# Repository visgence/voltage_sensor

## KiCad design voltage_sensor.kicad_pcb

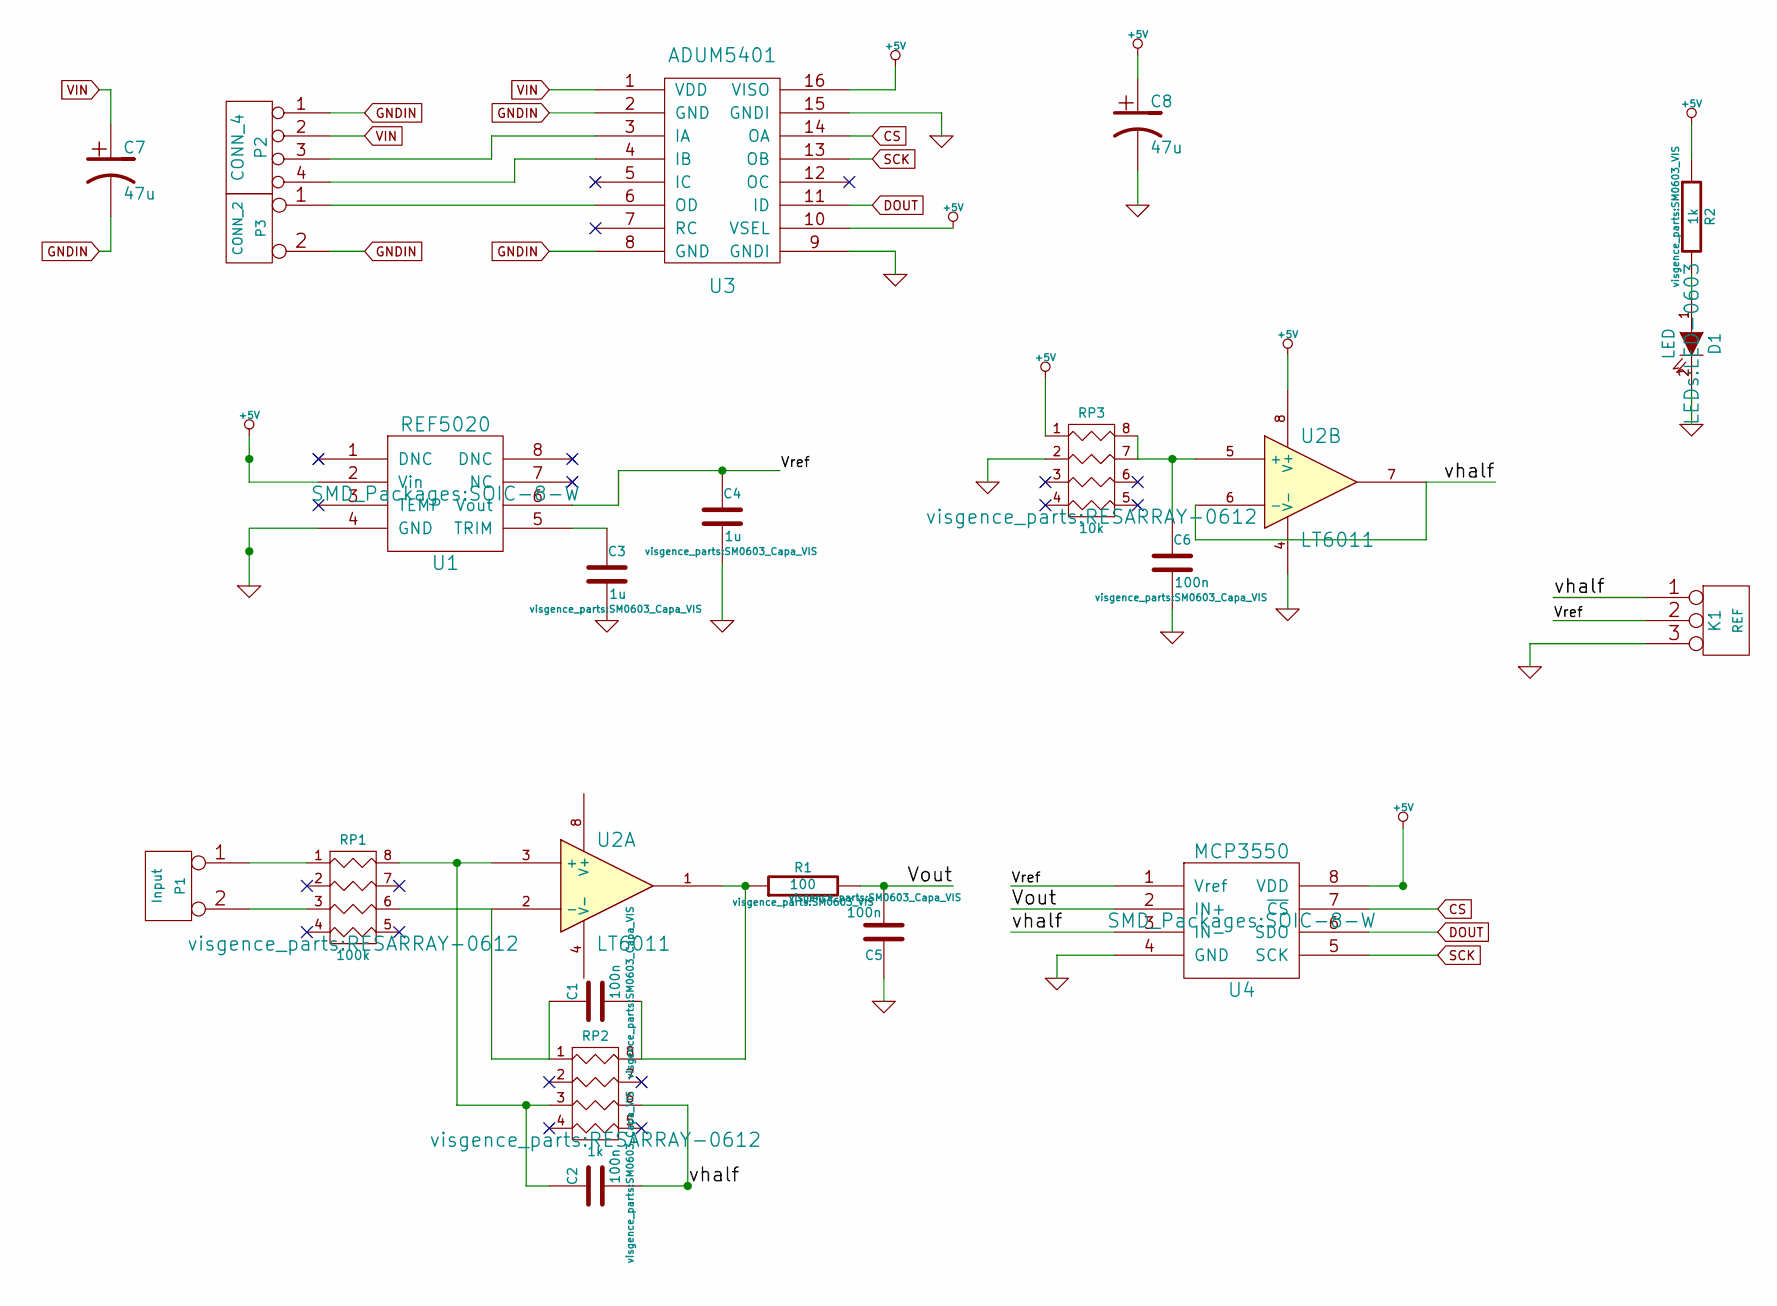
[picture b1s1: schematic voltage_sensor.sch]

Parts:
C1, C2, C5, C6: 100n; SM0603_Capa_VIS
C3, C4: 1u; SM0603_Capa_VIS
C7, C8: 47u; SM1206POL_VIS
D1: LED; LED-0603
K1: REF; Pin_Header_Straight_1x03
P1: Input; bornier2
P2: CONN_4; Term3.5-4
P3: CONN_2; Term3.5-2
R1: 100; SM0603_VIS
R2: 1k; SM0603_VIS
RP1: 100k; RESARRAY-0612
RP2: 1k; RESARRAY-0612
RP3: 10k; RESARRAY-0612
U1: REF5020; SOIC-8-W
U2: LT6011; SOIC-8-W
U3: ADUM5401; SO-16-W
U4: MCP3550; SOIC-8-W

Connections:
+5V: C8.1, R2.1, RP3.1, U1.2 (Vin), U2.8 (V+), U3.10 (VSEL), U3.16 (VISO), U4.8 (VDD)
/Vout: C5.2, R1.2, U4.2 (IN+)
/Vref: C4.1, K1.2 (PM), U1.6 (Vout), U4.1 (Vref)
/vhalf: C2.2, K1.1, RP2.6 (R3), U2.6 (-), U2.7, U4.3 (IN-)
CS: U3.14 (OA), U4.7 (~CS)
DOUT: U3.11 (ID), U4.6 (SDO)
GND: C3.2, C4.2, C5.1, C6.2, C8.2, D1.2 (K), K1.3, RP3.2, U1.4 (GND), U2.4 (V-), U3.9 (GNDI), U3.15 (GNDI), U4.4 (GND)
GNDIN: C7.2, P2.1, P3.2 (PM), U3.2 (GND), U3.8 (GND)
unnamed: C1.1, RP1.6 (R3), RP2.1, U2.2 (-)
unnamed: C1.2, R1.1, RP2.8 (R1), U2.1
unnamed: C2.1, RP1.8 (R1), RP2.3, U2.3 (+)
unnamed: C3.1, U1.5 (TRIM)
unnamed: C6.1, RP3.7 (R2), RP3.8 (R1), U2.5 (+)
unnamed: D1.1 (A), R2.2
unnamed: P1.1, RP1.1
unnamed: P1.2 (PM), RP1.3
unnamed: P2.3, U3.3 (IA)
unnamed: P2.4, U3.4 (IB)
unnamed: P3.1, U3.6 (OD)
SCK: U3.13 (OB), U4.5 (SCK)
VIN: C7.1, P2.2, U3.1 (VDD)

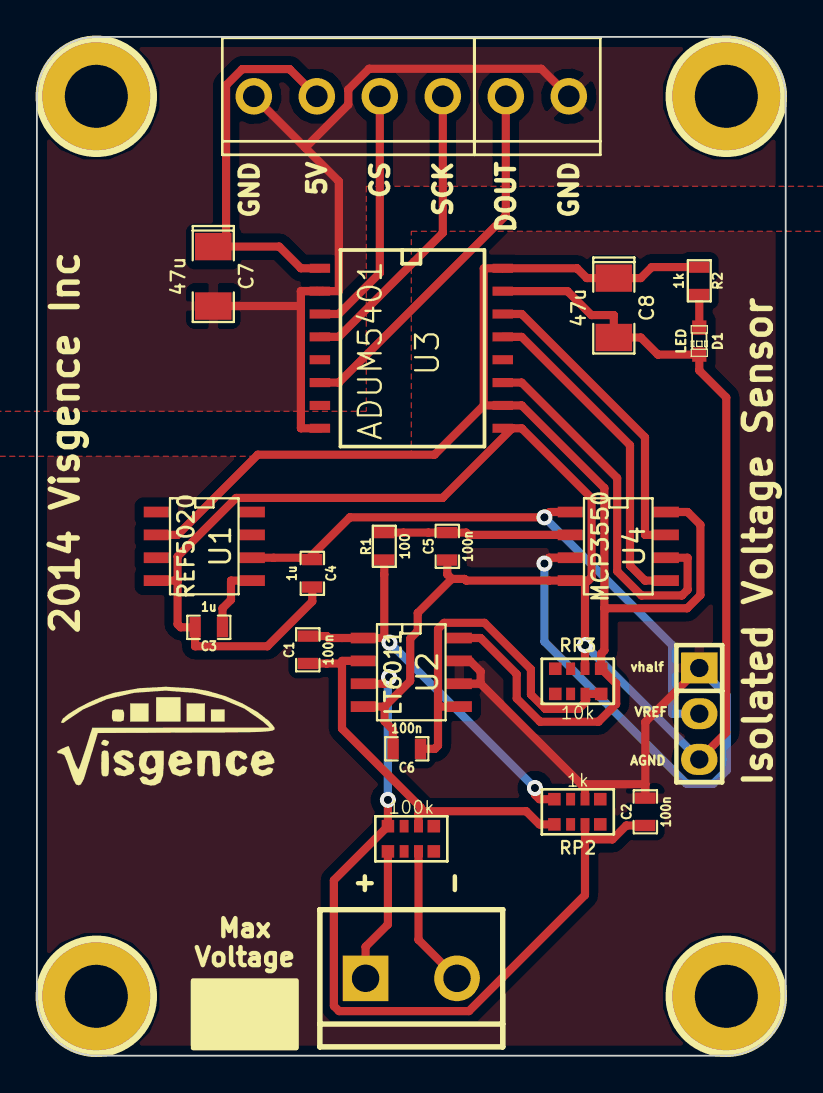
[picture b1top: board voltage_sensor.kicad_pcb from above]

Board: 2 copper layers, 41.6 x 56.6 mm, 27 parts (0 on the bottom side), 21 nets.

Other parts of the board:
G1: LOGO
h1, h2, h3, h4: pin; 1pin_C

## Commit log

2014-08-14 First commit of voltage_sensor
2014-08-14 Started routing board
2014-08-14 Added filter caps
2014-08-14 Routed board
2014-08-19 Changed Opamp to chopper
